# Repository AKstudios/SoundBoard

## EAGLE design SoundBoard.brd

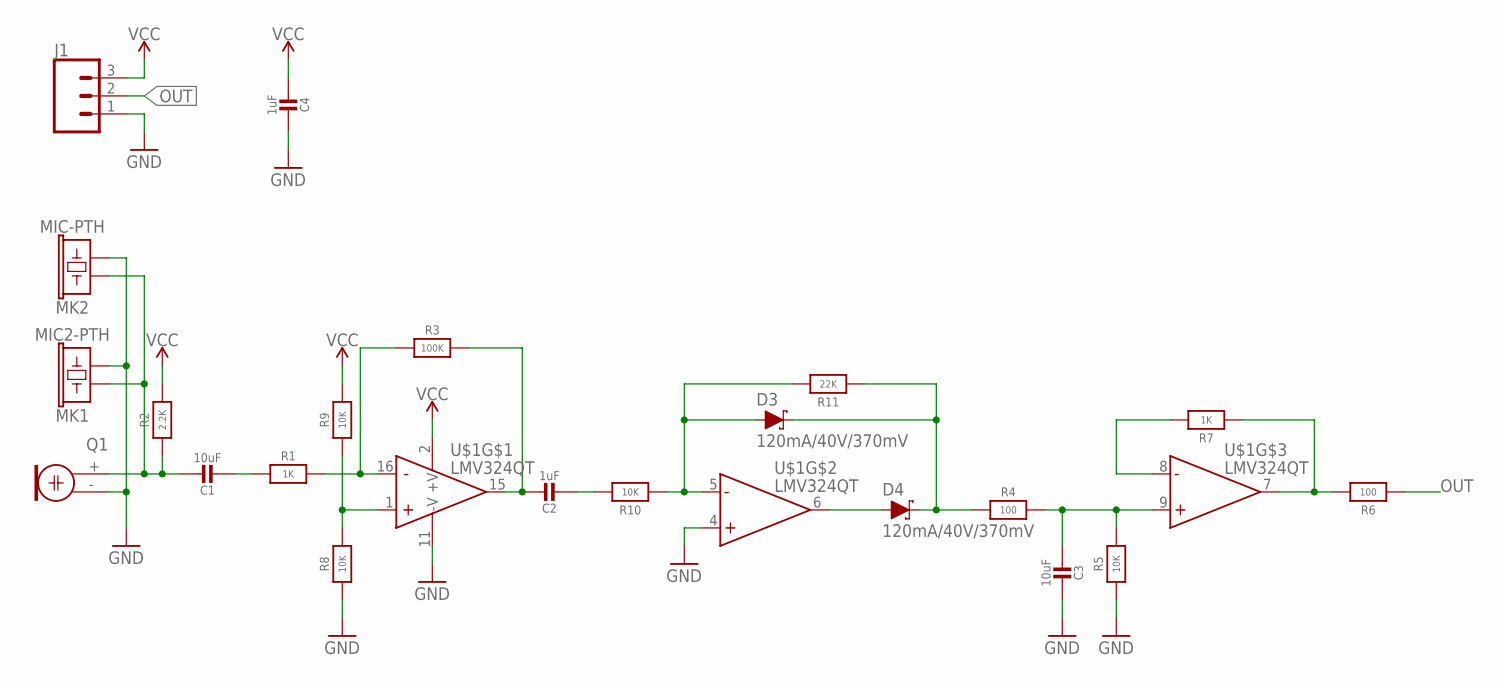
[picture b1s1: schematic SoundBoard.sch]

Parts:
C1, C3: 10uF; MICROBUILDER__0402MP
C2, C4: 1uF; MICROBUILDER__0402MP
D3, D4: 120mA/40V/370mV; SOD-523
J1: CONN_03; 1X03
MK1: MIC2-PTH; MICROPHONE-PTH-4.0MM
MK2: MIC-PTH; MICROPHONE-PTH-4.0MM
Q1: ELECTRET; 9.7ELECTRET
R1, R7: 1K; MICROBUILDER__0402MP
R2: 2.2K; MICROBUILDER__0402MP
R3: 100K; MICROBUILDER__0402MP
R4, R6: 100; MICROBUILDER__0402MP
R5, R8, R9, R10: 10K; MICROBUILDER__0402MP
R11: 22K; MICROBUILDER__0402MP
U$1: LMV324QT; QFN-16_3X3

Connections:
AMP: C2.1, R3.2, U$1.15 (OUT)
GND: C3.1, C4.1, J1.1, MK1.GND (2), MK2.GND (2), Q1.- (1), R5.1, R8.1, U$1.4 (+IN), U$1.11 (-V)
unnamed: C1.2, R1.1
unnamed: R1.2, R3.1, U$1.16 (-IN)
unnamed: D4.A, U$1.6 (OUT)
unnamed: R7.2, U$1.8 (-IN)
unnamed: D3.A, R10.1, R11.2, U$1.5 (-IN)
unnamed: D3.C, D4.C, R4.1, R11.1
unnamed: C2.2, R10.2
unnamed: C3.2, R4.2, R5.2, U$1.9 (+IN)
unnamed: C1.1, MK1.OUT (1), MK2.OUT (1), Q1.+ (2), R2.1
OUT: J1.2, R6.1
VCC: C4.2, J1.3, R2.2, R9.2, U$1.2 (+V)
VCC/2: R8.2, R9.1, U$1.1 (+IN)
_OUT: R6.2, R7.1, U$1.7 (OUT)

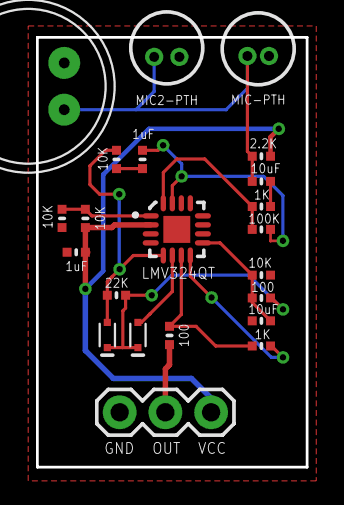
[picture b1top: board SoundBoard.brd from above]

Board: 2 copper layers, 15.0 x 23.9 mm, 22 parts (0 on the bottom side), 15 nets.

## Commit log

2017-08-07 :lollipop: Added .gitattributes & .gitignore files
2017-08-07 init
2017-08-15 v2 - updated OPAMP to LM324QT
    - rerouted traces to accomodate for new QFN part
    - Added electret microphone pins to test both
    - rearranged some parts
    - increased board dimensions slightly
2017-09-12 v3 - replaced MEMS mic with electret mic (adjusted circuitry)

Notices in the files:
parts and their libraries:
SparkFun-Connectors: Licensing: Creative Commons ShareAlike 4.0 International - https://creativecommons.org/licenses/by-sa/4.0
